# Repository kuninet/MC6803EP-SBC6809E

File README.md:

# SBC6809Eルーズキット用 MC6803EP MPUアダプタ

## 概要

* SBC6809Eルーズキットに MC6803EP MPUを搭載するアダプタ基板です。
* SBC6809Eルーズキットに載っているMC6883のE信号から、MC6803EPのE信号/AS信号を生成する回路がのってます。

## 参考

* [SBC6809Eが完成](https://vintagechips.wordpress.com/2022/01/06/sbc6809e_reference/)

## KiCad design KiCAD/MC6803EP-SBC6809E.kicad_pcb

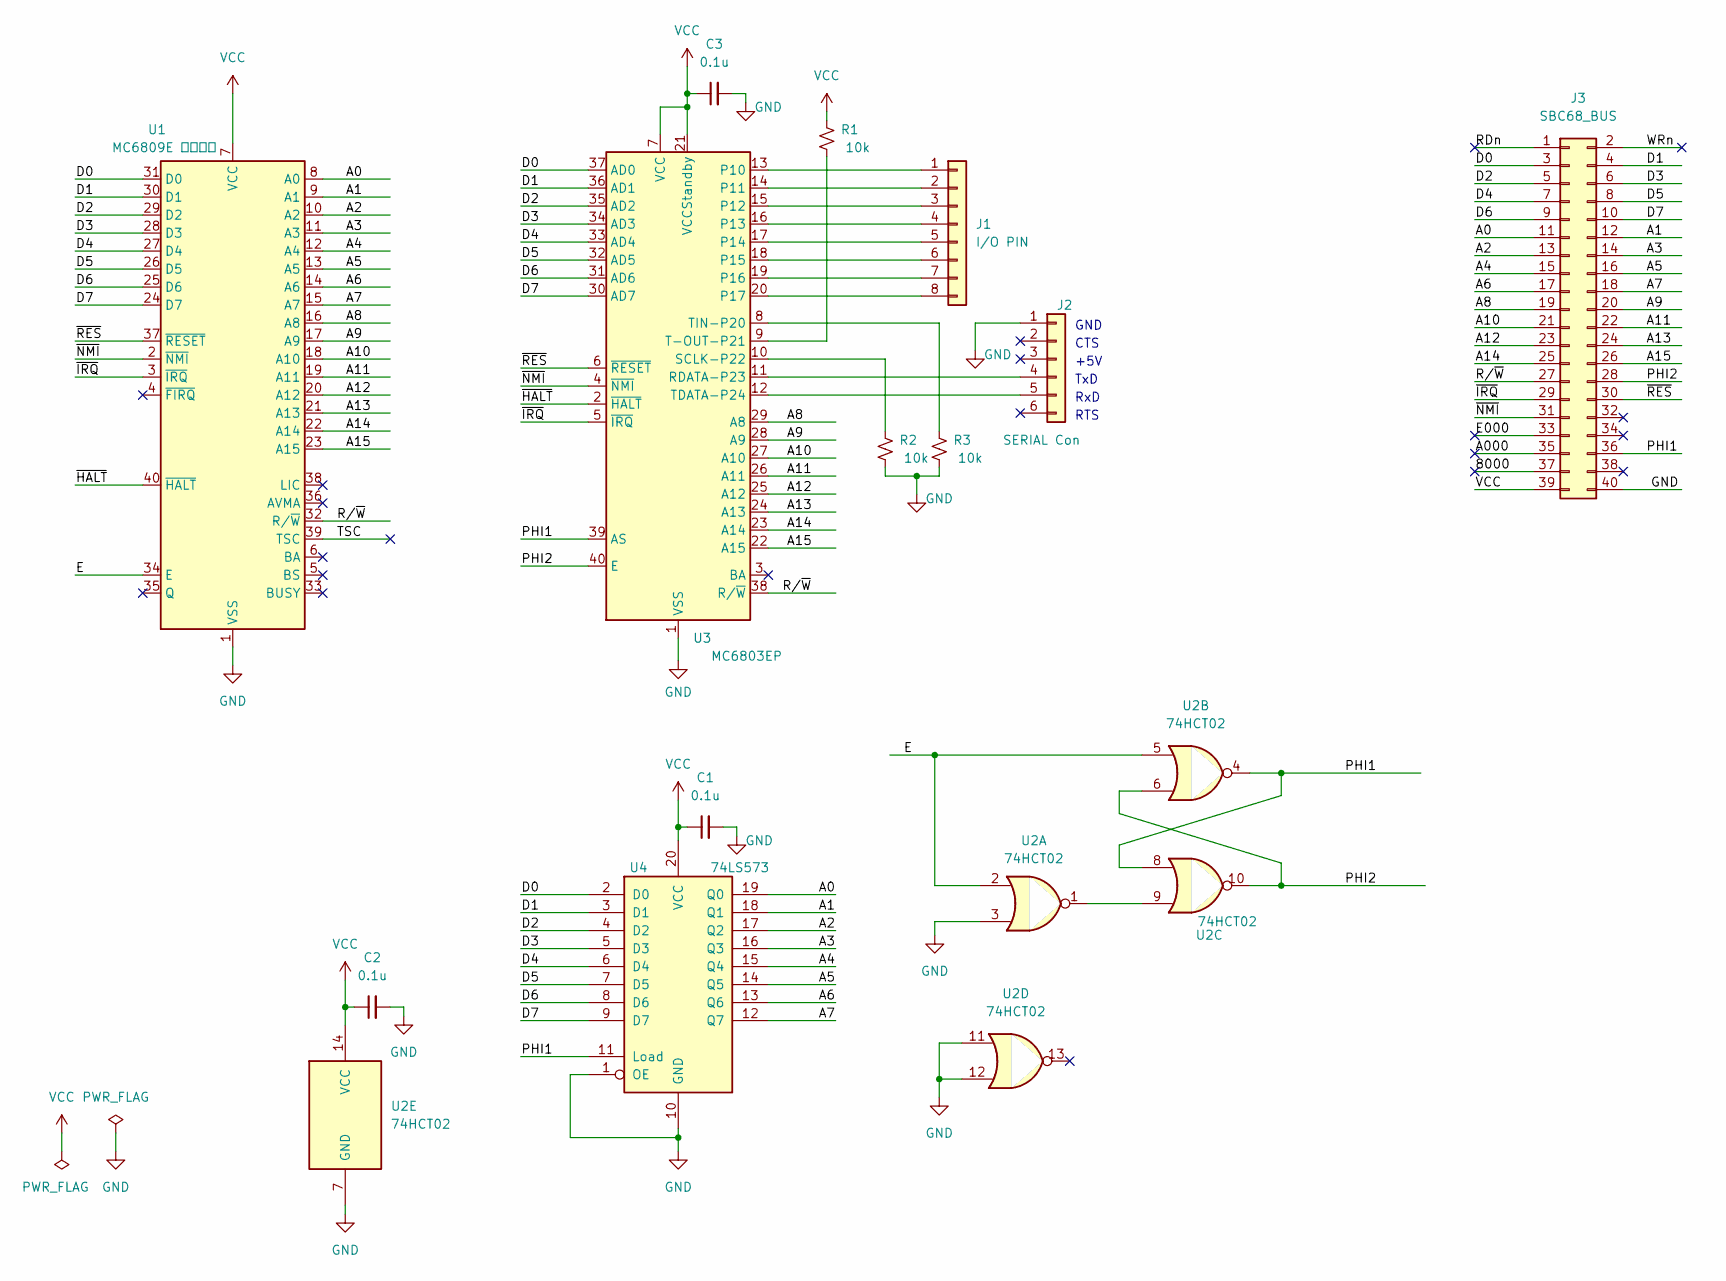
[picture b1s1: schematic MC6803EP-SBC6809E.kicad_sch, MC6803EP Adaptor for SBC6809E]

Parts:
C1, C2, C3: 0.1u; C_Disc_D3.0mm_W1.6mm_P2.50mm
J1: I/O PIN; PinHeader_1x08_P2.54mm_Horizontal
J2: SERIAL Con; PinHeader_1x06_P2.54mm_Horizontal
J3: SBC68_BUS; PinHeader_2x20_P2.54mm_Horizontal
R1, R2, R3: 10k; R_Axial_DIN0207_L6.3mm_D2.5mm_P10.16mm_Horizontal
U1: MC6809E ソケット; DIP-40_W15.24mm_Socket
U2: 74HCT02; DIP-14_W7.62mm_Socket
U3: MC6803EP; DIP-40_W15.24mm_Socket
U4: 74LS573; DIP-20_W7.62mm_Socket

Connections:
/8000: J3.37
/A0: J3.11, U1.8 (A0), U4.19 (Q0)
/A000: J3.35
/A1: J3.12, U1.9 (A1), U4.18 (Q1)
/A2: J3.13, U1.10 (A2), U4.17 (Q2)
/A3: J3.14, U1.11 (A3), U4.16 (Q3)
/A4: J3.15, U1.12 (A4), U4.15 (Q4)
/A5: J3.16, U1.13 (A5), U4.14 (Q5)
/A6: J3.17, U1.14 (A6), U4.13 (Q6)
/A7: J3.18, U1.15 (A7), U4.12 (Q7)
/A8: J3.19, U1.16 (A8), U3.29 (A8)
/A9: J3.20, U1.17 (A9), U3.28 (A9)
/A10: J3.21, U1.18 (A10), U3.27 (A10)
/A11: J3.22, U1.19 (A11), U3.26 (A11)
/A12: J3.23, U1.20 (A12), U3.25 (A12)
/A13: J3.24, U1.21 (A13), U3.24 (A13)
/A14: J3.25, U1.22 (A14), U3.23 (A14)
/A15: J3.26, U1.23 (A15), U3.22 (A15)
/D0: J3.3, U1.31 (D0), U3.37 (AD0), U4.2 (D0)
/D1: J3.4, U1.30 (D1), U3.36 (AD1), U4.3 (D1)
/D2: J3.5, U1.29 (D2), U3.35 (AD2), U4.4 (D2)
/D3: J3.6, U1.28 (D3), U3.34 (AD3), U4.5 (D3)
/D4: J3.7, U1.27 (D4), U3.33 (AD4), U4.6 (D4)
/D5: J3.8, U1.26 (D5), U3.32 (AD5), U4.7 (D5)
/D6: J3.9, U1.25 (D6), U3.31 (AD6), U4.8 (D6)
/D7: J3.10, U1.24 (D7), U3.30 (AD7), U4.9 (D7)
/E: U1.34 (E), U2.2, U2.5
/E000: J3.33
/PHI1: J3.36, U2.4, U2.8, U3.39 (AS), U4.11 (Load)
/PHI2: J3.28, U2.6, U2.10, U3.40 (E)
/RDn: J3.1
/R/~W: J3.27, U1.32 (R/~W), U3.38 (R/~W)
/TSC: U1.39 (TSC)
/WRn: J3.2
/~HALT: U1.40 (~HALT), U3.2 (~HALT)
/~IRQ: J3.29, U1.3 (~IRQ), U3.5 (~IRQ)
/~NMI: J3.31, U1.2 (~NMI), U3.4 (~NMI)
/~RES: J3.30, U1.37 (~RESET), U3.6 (~RESET)
GND: C1.2, C2.2, C3.2, J2.1, J3.40, R2.2, R3.2, U1.1 (VSS), U2.3, U2.7 (GND), U2.11, U2.12, U3.1 (VSS), U4.1 (OE), U4.10 (GND)
unnamed: J1.1, U3.13 (P10)
unnamed: J1.2, U3.14 (P11)
unnamed: J1.3, U3.15 (P12)
unnamed: J1.4, U3.16 (P13)
unnamed: J1.5, U3.17 (P14)
unnamed: J1.6, U3.18 (P15)
unnamed: J1.7, U3.19 (P16)
unnamed: J1.8, U3.20 (P17)
unnamed: J2.4, U3.11 (RDATA-P23)
unnamed: J2.5, U3.12 (TDATA-P24)
unnamed: U2.1, U2.9
unnamed: R2.1, U3.10 (SCLK-P22)
unnamed: R1.2, U3.9 (T-OUT-P21)
unnamed: R3.1, U3.8 (TIN-P20)
VCC: C1.1, C2.1, C3.1, J3.39, R1.1, U1.7 (VCC), U2.14 (VCC), U3.7 (VCC), U3.21 (VCCStandby), U4.20 (VCC)

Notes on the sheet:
TxD
+5V
RTS
GND
RxD
CTS

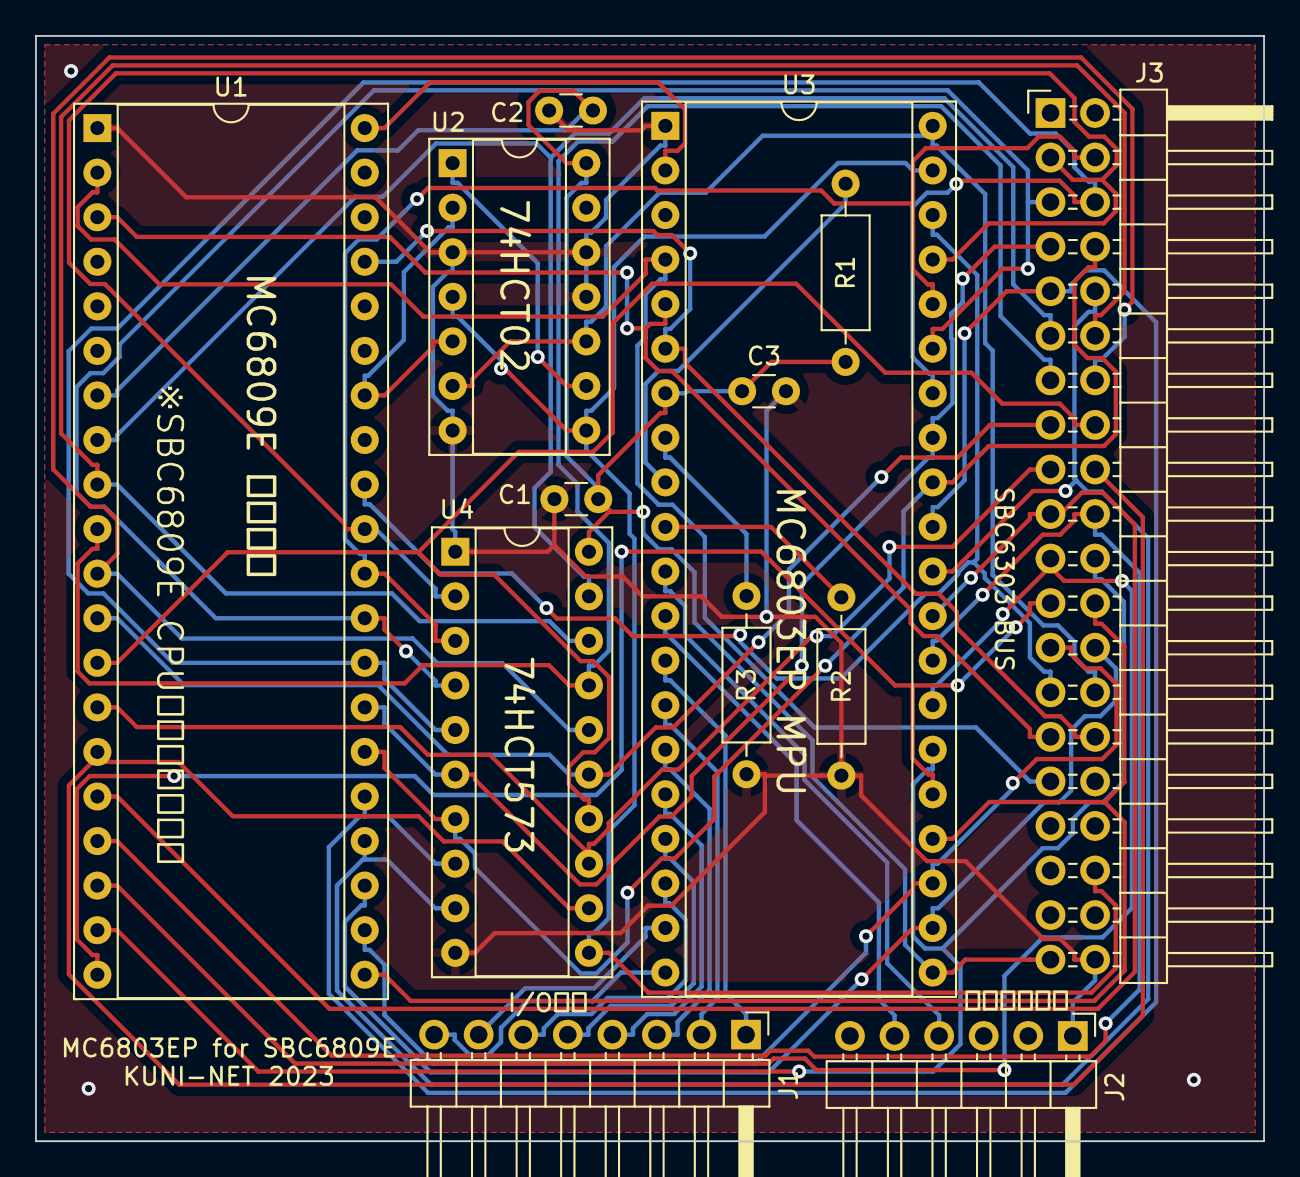
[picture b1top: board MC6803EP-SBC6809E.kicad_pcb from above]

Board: 2 copper layers, 70.0 x 63.0 mm, 13 parts (0 on the bottom side), 48 nets.

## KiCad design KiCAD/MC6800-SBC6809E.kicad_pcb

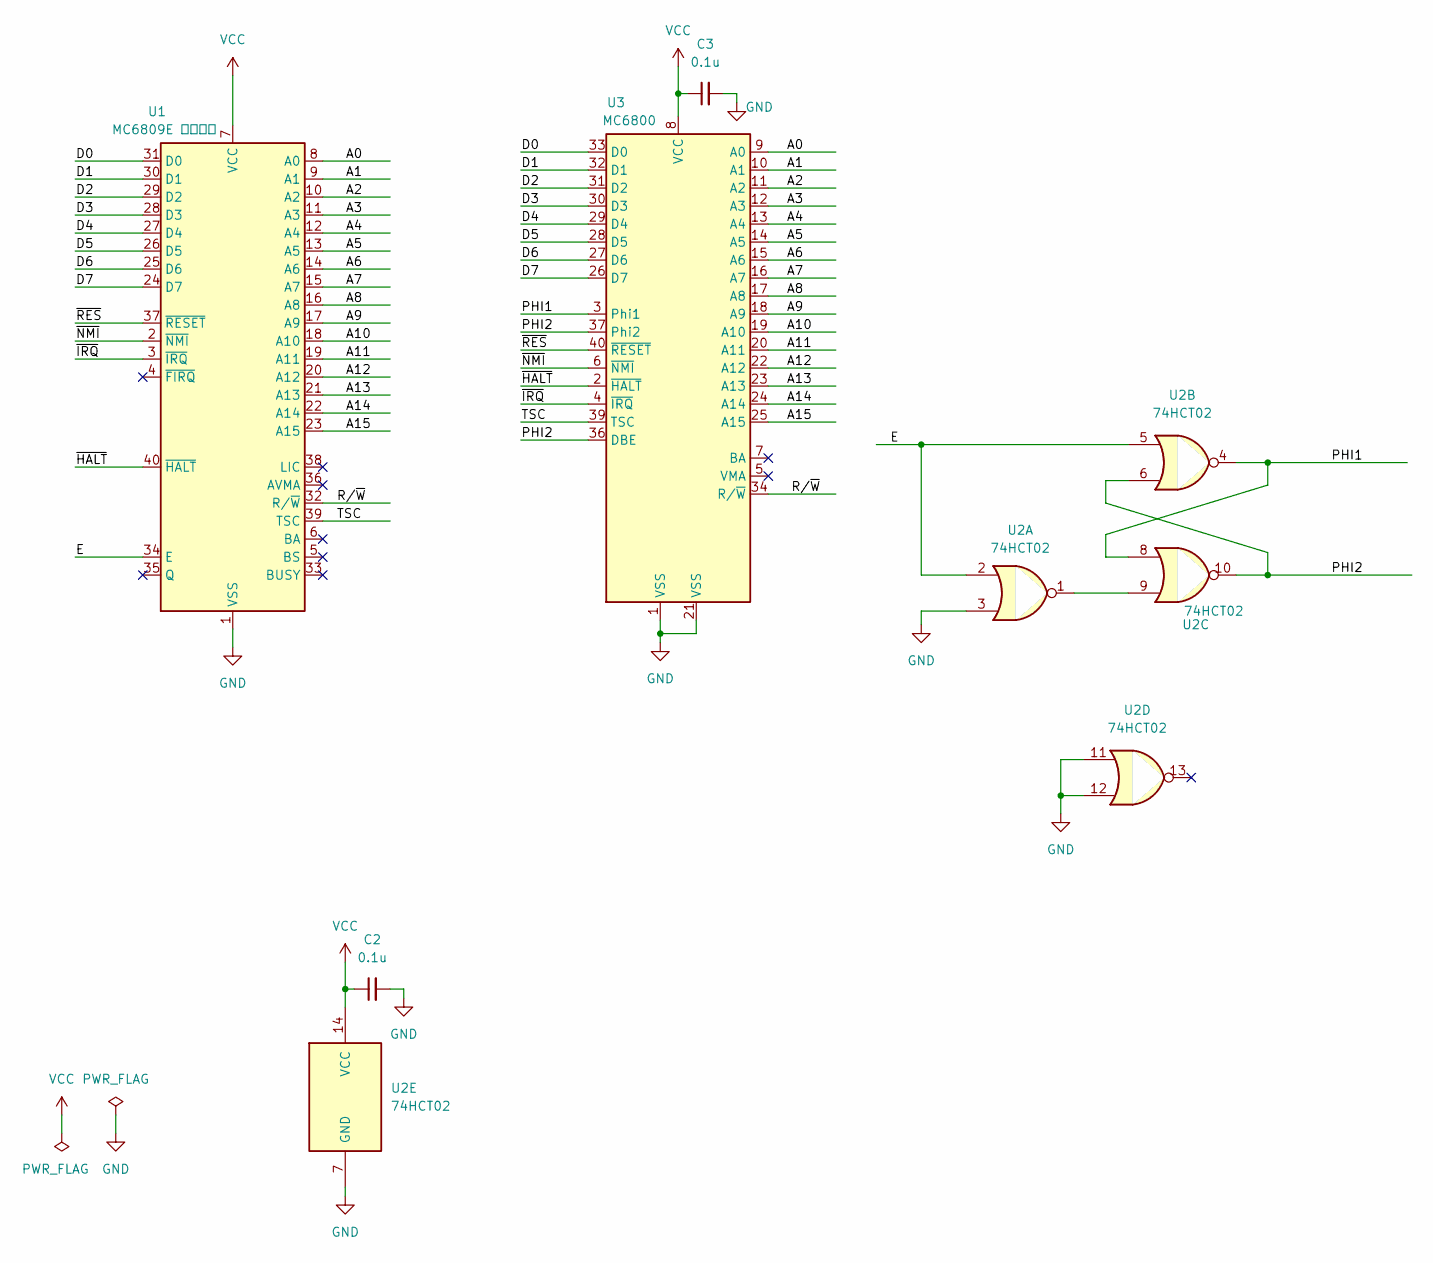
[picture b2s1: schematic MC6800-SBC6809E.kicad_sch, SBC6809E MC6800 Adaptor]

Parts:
C2, C3: 0.1u; C_Disc_D3.0mm_W1.6mm_P2.50mm
U1: MC6809E ソケット; DIP-40_W15.24mm_Socket_LongPads
U2: 74HCT02; DIP-14_W7.62mm_Socket_LongPads
U3: MC6800; DIP-40_W15.24mm_Socket_LongPads

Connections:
/A0: U1.8 (A0), U3.9 (A0)
/A1: U1.9 (A1), U3.10 (A1)
/A2: U1.10 (A2), U3.11 (A2)
/A3: U1.11 (A3), U3.12 (A3)
/A4: U1.12 (A4), U3.13 (A4)
/A5: U1.13 (A5), U3.14 (A5)
/A6: U1.14 (A6), U3.15 (A6)
/A7: U1.15 (A7), U3.16 (A7)
/A8: U1.16 (A8), U3.17 (A8)
/A9: U1.17 (A9), U3.18 (A9)
/A10: U1.18 (A10), U3.19 (A10)
/A11: U1.19 (A11), U3.20 (A11)
/A12: U1.20 (A12), U3.22 (A12)
/A13: U1.21 (A13), U3.23 (A13)
/A14: U1.22 (A14), U3.24 (A14)
/A15: U1.23 (A15), U3.25 (A15)
/D0: U1.31 (D0), U3.33 (D0)
/D1: U1.30 (D1), U3.32 (D1)
/D2: U1.29 (D2), U3.31 (D2)
/D3: U1.28 (D3), U3.30 (D3)
/D4: U1.27 (D4), U3.29 (D4)
/D5: U1.26 (D5), U3.28 (D5)
/D6: U1.25 (D6), U3.27 (D6)
/D7: U1.24 (D7), U3.26 (D7)
/E: U1.34 (E), U2.2, U2.5
/PHI1: U2.4, U2.8, U3.3 (Phi1)
/PHI2: U2.6, U2.10, U3.36 (DBE), U3.37 (Phi2)
/R/~W: U1.32 (R/~W), U3.34 (R/~W)
/TSC: U1.39 (TSC), U3.39 (TSC)
/~HALT: U1.40 (~HALT), U3.2 (~HALT)
/~IRQ: U1.3 (~IRQ), U3.4 (~IRQ)
/~NMI: U1.2 (~NMI), U3.6 (~NMI)
/~RES: U1.37 (~RESET), U3.40 (~RESET)
GND: C2.2, C3.2, U1.1 (VSS), U2.3, U2.7 (GND), U2.11, U2.12, U3.1 (VSS), U3.21 (VSS)
unnamed: U2.1, U2.9
VCC: C2.1, C3.1, U1.7 (VCC), U2.14 (VCC), U3.8 (VCC)

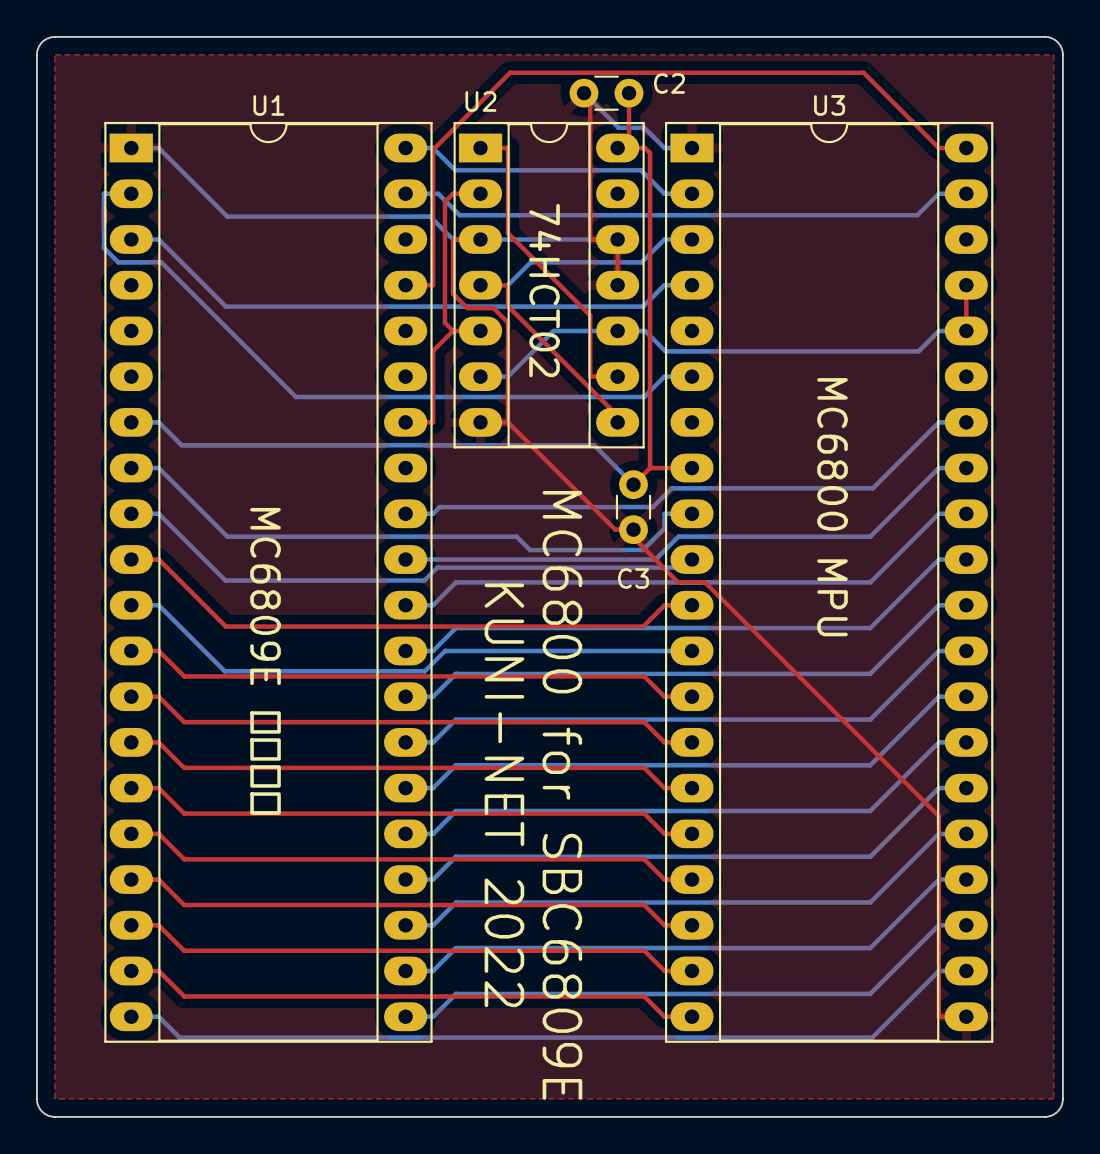
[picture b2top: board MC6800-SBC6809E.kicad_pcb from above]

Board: 2 copper layers, 57.0 x 60.0 mm, 5 parts (0 on the bottom side), 36 nets.

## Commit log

2022-11-05 init commit
2022-11-05 REV1 回路図・ガーバーデータ出力
2022-11-24 MC6803E 対応回路図作成
2022-12-18 REV1 ガーバーデータ出力
2022-12-18 README間違い修正
2022-12-18 回路図イメージ差し替え
2023-03-04 REV1 回路変更(シリアル端子)、ガーバー再出力
2023-03-04 回路図 PDF/jpeg差し替え
